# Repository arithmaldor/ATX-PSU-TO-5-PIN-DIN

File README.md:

# Copyright and Disclaimer
Copyright: Jacob Proctor 2018

This documentation describes Open Hardware and is licensed under the
CERN OHL v. 1.2.

You may redistribute and modify this documentation under the terms of the
CERN OHL v.1.2. (http://ohwr.org/cernohl). This documentation is distributed
WITHOUT ANY EXPRESS OR IMPLIED WARRANTY, INCLUDING OF
MERCHANTABILITY, SATISFACTORY QUALITY AND FITNESS FOR A
PARTICULAR PURPOSE. Please see the CERN OHL v.1.2 for applicable
conditions

# ATX to Extron Emotia PSU Adapter

Please please please know what you are doing and be careful if you decide to use this. It is untested and if I got something backwards it could fry your emotia.

That aside, this should let you power your emotia downscaler with an off the shelf psu instead of shelling out for a very expensive OEM one.

BOM is in the "Documentation" folder. Just 3 parts.

# Version 0.1
This board is untested.

# OSHPark
https://oshpark.com/shared_projects/UrYD28fo

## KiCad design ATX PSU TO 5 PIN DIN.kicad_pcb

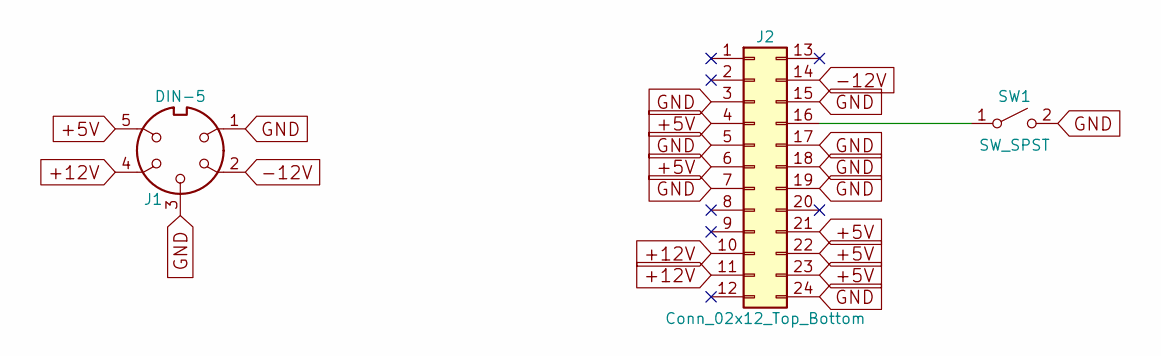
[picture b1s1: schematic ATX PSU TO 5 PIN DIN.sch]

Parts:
J1: DIN-5; DIN_8
J2: Conn_02x12_Top_Bottom; ATX_PWR_24
SW1: SW_SPST; SPDT_A12AV1

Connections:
+5V: J1.5, J2.4, J2.6, J2.21, J2.22, J2.23
+12V: J1.4, J2.10, J2.11
-12V: J1.2, J2.14
GND: J1.1, J1.3, J2.3, J2.5, J2.7, J2.15, J2.17, J2.18, J2.19, J2.24, SW1.2 (B)
unnamed: J2.16, SW1.1 (A)

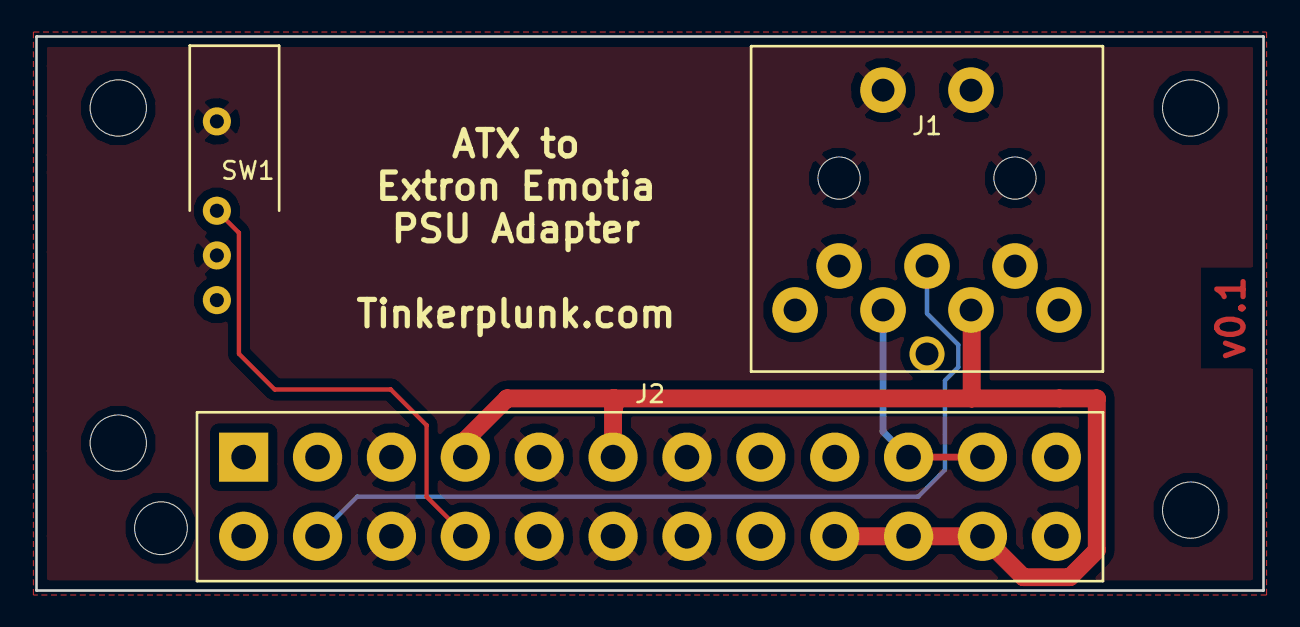
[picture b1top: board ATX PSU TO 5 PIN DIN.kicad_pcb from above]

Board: 2 copper layers, 69.8 x 31.5 mm, 3 parts (0 on the bottom side), 5 nets.

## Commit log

2018-07-10 0.2 Untested
2018-07-10 BOM location
